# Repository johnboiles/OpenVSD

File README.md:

OpenVSD
=======
http://github.com/johnboiles/OpenVSD

A small board and accompanying Arduino firmware that allows you to turn a normal diaphragm pump into a variable speed diaphragm pump.

Bill of Materials
-----------------
1x 5V Pressure Sensor

1x IRFZ40 High-power MOSFET

1x MCP1416 MOSFET Driver

2x 0.1uF Capacitor

1x 1uF Capacitor

1x 5V Sparkfun Arduino Pro Micro 

TODO
____
Add flyback diode

Better footprint for screw terminals

Proper footprint for film capacitor

Silkscreen to indicate orientation of Arduino

Switch to default back to pressure switch

Debug LEDs

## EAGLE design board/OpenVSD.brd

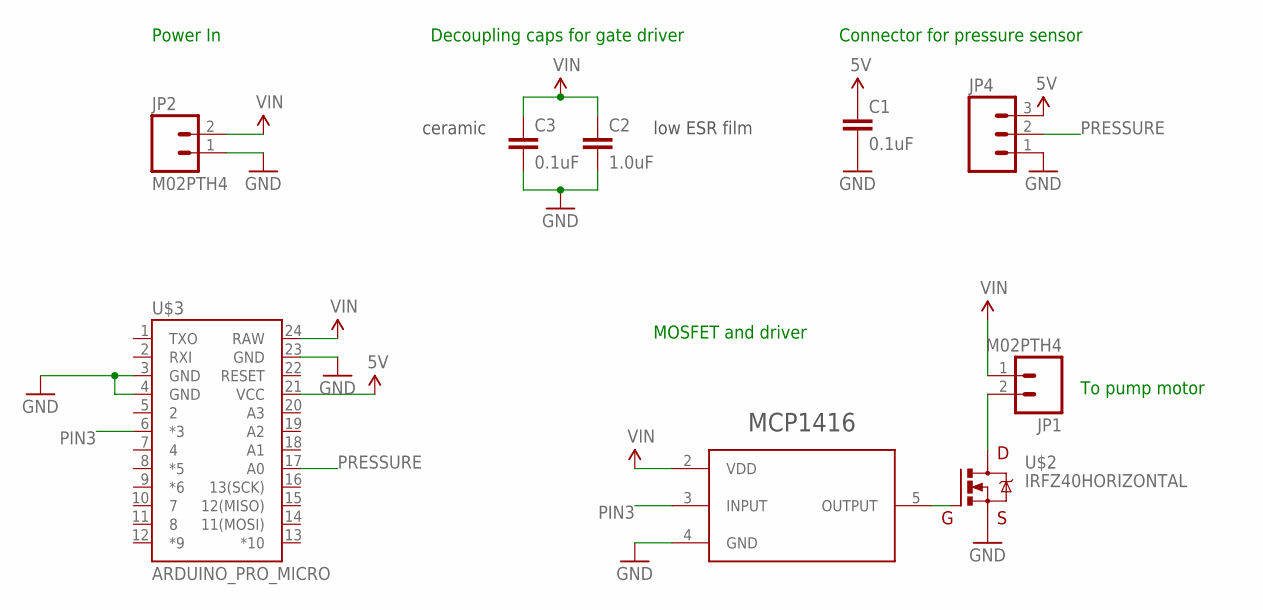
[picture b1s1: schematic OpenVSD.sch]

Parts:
C1, C3: 0.1uF; 0603-CAP
C2: 1.0uF; 0603-CAP
JP1, JP2: M02PTH4; 1X02_XTRA_BIG
JP4: M03PTH; 1X03
U$1: MCP1416; SOT23-5
U$2: IRFZ40HORIZONTAL; TO220
U$3: ARDUINO_PRO_MICRO

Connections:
5V: C1.1, JP4.3, U$3.21 (VCC)
GND: C1.2, C2.2, C3.2, JP2.1, JP4.1, U$1.4 (GND), U$2.3 (S), U$3.3 (GND), U$3.4 (GND), U$3.23 (GND)
unnamed: U$1.5 (OUTPUT), U$2.1 (G)
PIN3: U$1.3 (INPUT), U$3.6 (*3)
PRESSURE: JP4.2, U$3.17 (A0)
PUMP-: JP1.2, U$2.2 (D)
VIN: C2.1, C3.1, JP1.1, JP2.2, U$1.2 (VDD), U$3.24 (RAW)

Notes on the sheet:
low ESR film
ceramic
Power In
Decoupling caps for gate driver
Connector for pressure sensor
MOSFET and driver
To pump motor

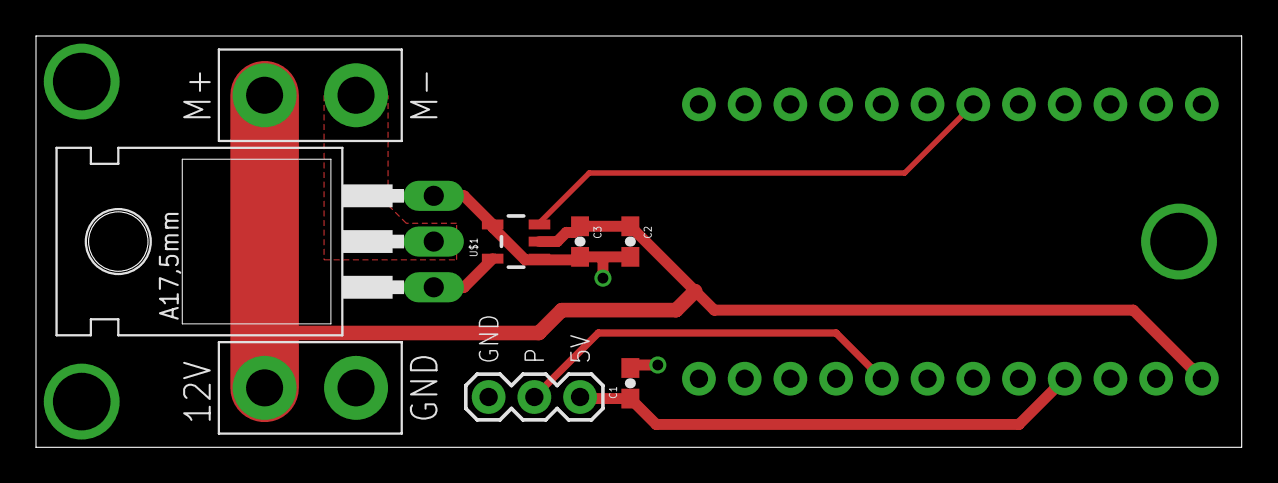
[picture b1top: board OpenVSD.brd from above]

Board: 2 copper layers, 67.0 x 22.9 mm, 9 parts (0 on the bottom side), 7 nets.

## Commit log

2014-04-23 WIP on speed controller firmware
2014-04-23 Using OCR interrupts for a more timely pid
2014-04-30 Working PID controller firmware

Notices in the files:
parts and their libraries:
SparkFun-Boards: Licensing: Creative Commons ShareAlike 4.0 International - https://creativecommons.org/licenses/by-sa/4.0
